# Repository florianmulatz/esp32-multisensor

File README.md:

Project archived because there is already a active GitHub project on this topic which is promising.

[GiThub Project of AIOsense](https://github.com/Schluggi/AIOsense/tree/v2.0)

Cheers

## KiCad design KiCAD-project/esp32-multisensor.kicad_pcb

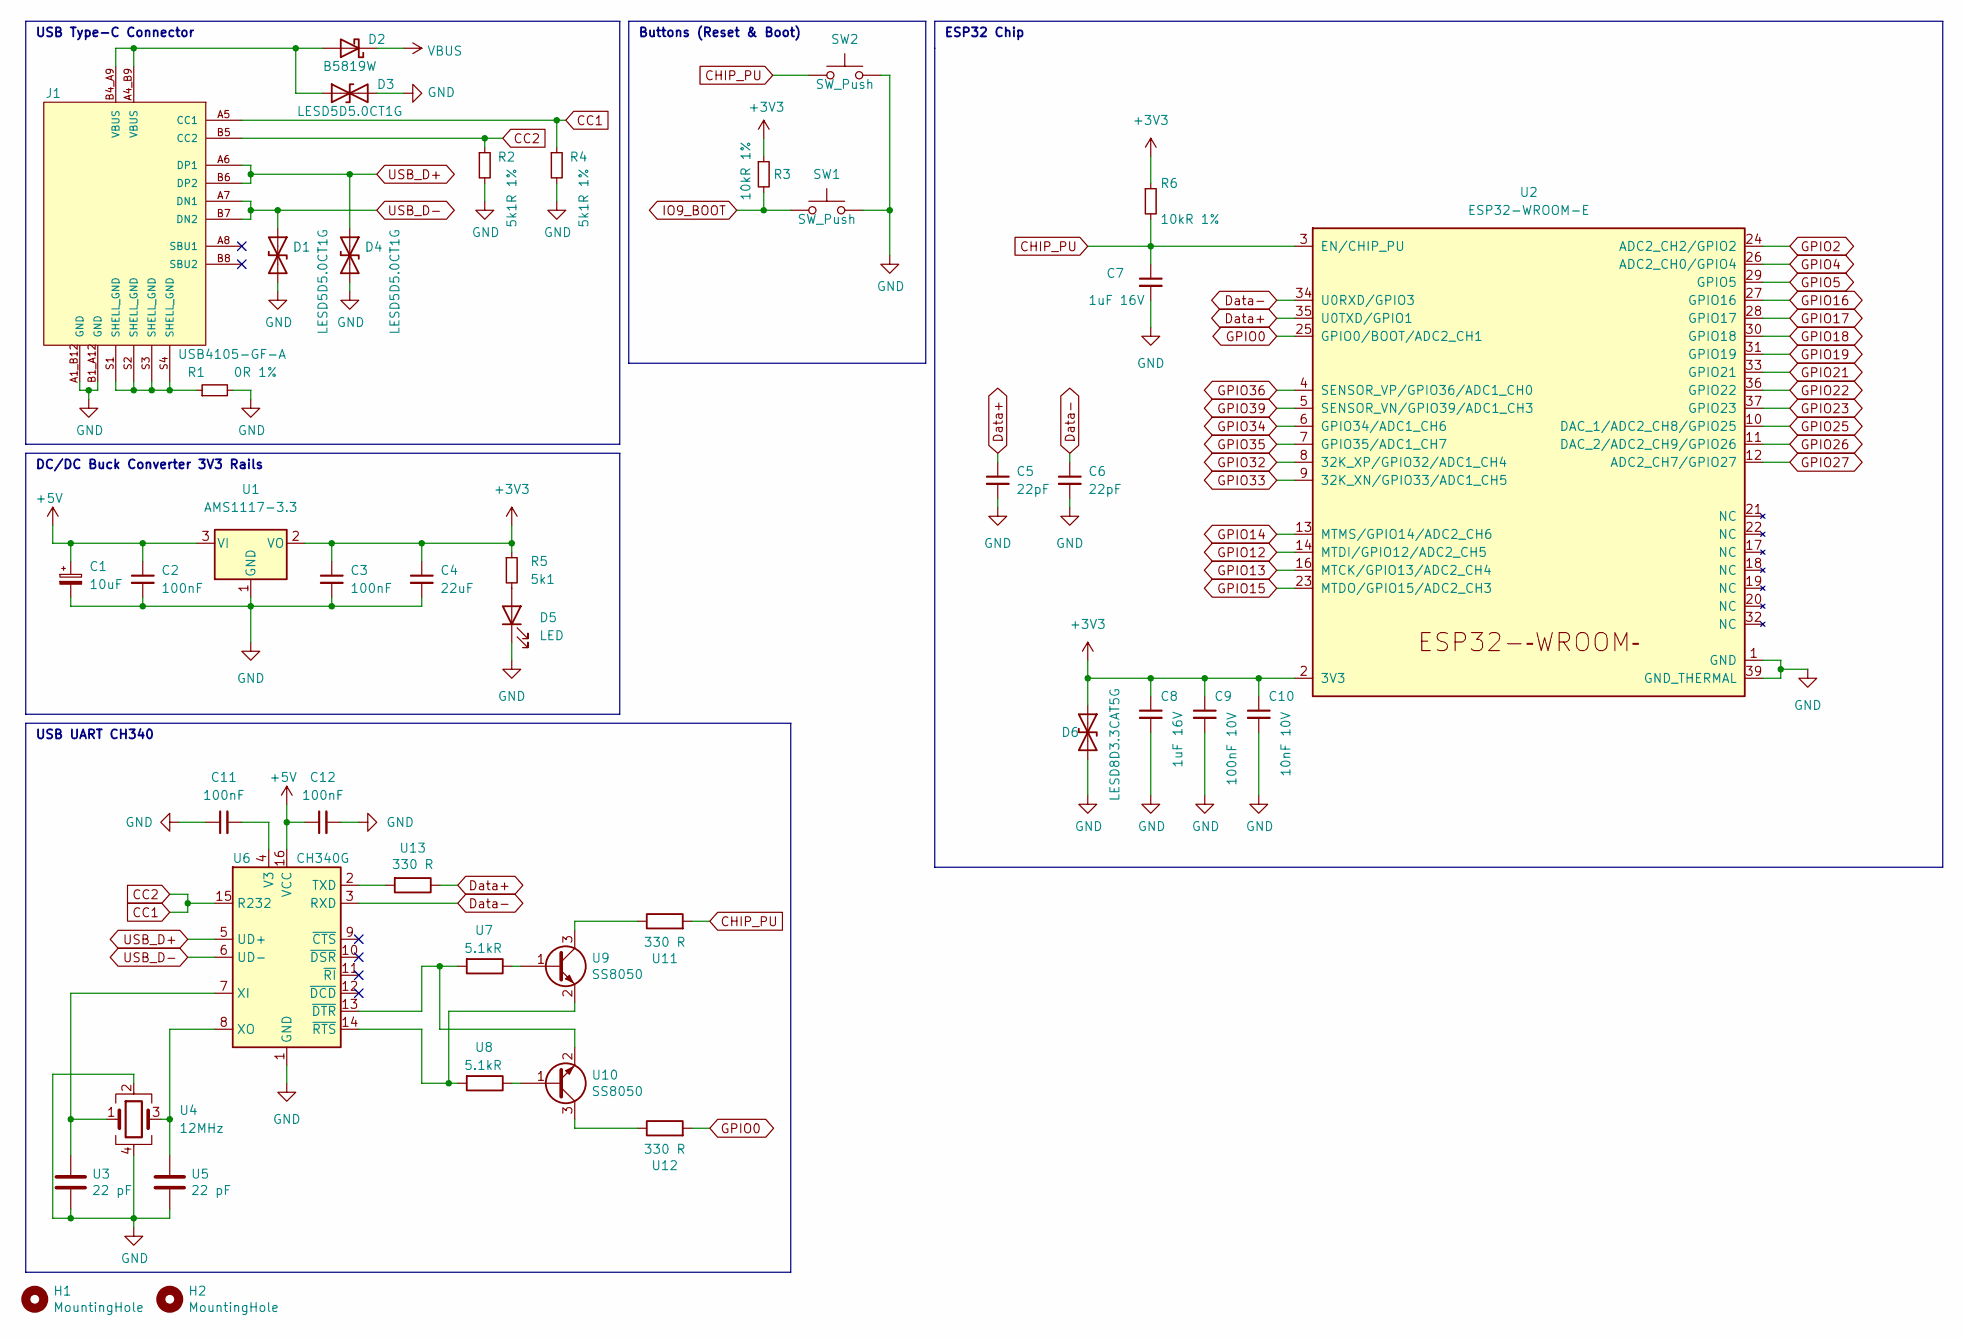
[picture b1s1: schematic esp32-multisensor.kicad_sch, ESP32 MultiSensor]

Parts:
C1: 10uF; CP_Radial_Tantal_D4.5mm_P2.50mm
C2, C3, C11, C12: 100nF; CP_Radial_D5.0mm_P2.50mm
C4: 22uF; CP_Radial_D5.0mm_P2.50mm
C5, C6: 22pF; CP_Radial_D5.0mm_P2.50mm
C7, C8: 1uF 16V; CP_Radial_D5.0mm_P2.50mm
C9: 100nF 10V; CP_Radial_D5.0mm_P2.50mm
C10: 10nF 10V; CP_Radial_D5.0mm_P2.50mm
D1, D4: LESD5D5.0CT1G; D_SOD-123; LCSC C2960981
D2: B5819W; D_A-405_P10.16mm_Horizontal; LCSC 1861420
D3: LESD5D5.0CT1G; D_SOD-923; FARNELL 3287352RL
D5: LED; LED_0805_2012Metric_Pad1.15x1.40mm_HandSolder
D6: LESD8D3.3CAT5G; SOD-882; LCSC C172409
H1, H2: MountingHole; ToolingHole_JLCSMT
J1: USB4105-GF-A; GCT_USB4105-GF-A; FARNELL 3588199
R1: 0R 1%; R_Axial_DIN0207_L6.3mm_D2.5mm_P10.16mm_Horizontal; FARNELL 2329957
R2, R4: 5k1R 1%; R_Axial_DIN0207_L6.3mm_D2.5mm_P10.16mm_Horizontal; FARNELL 2329957
R3, R6: 10kR 1%; R_Axial_DIN0207_L6.3mm_D2.5mm_P10.16mm_Horizontal; FARNELL 2329855
R5: 5k1; R_Axial_DIN0207_L6.3mm_D2.5mm_P10.16mm_Horizontal
SW1, SW2: SW_Push; SW_147873-2; LCSC C116501
U1: AMS1117-3.3; SOT-223-3_TabPin2
U2: ESP32-WROOM-E; ESP32-WROOM-32E
U3, U5: 22 pF; C_0402_1005Metric; LCSC C1555
U4: 12MHz; Crystal_SMD_3225-4Pin_3.2x2.5mm; LCSC C9002
U6: CH340G; SOIC-16_3.9x9.9mm_P1.27mm; LCSC C14267
U7, U8: 5.1kR; R_0402_1005Metric; LCSC C25905
U9, U10: SS8050; SOT-23; LCSC C2150
U11, U12, U13: 330 R; R_0402_1005Metric; LCSC C25104

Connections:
+3V3: C3.1, C4.1, C8.1, C9.1, C10.1, D6.1 (A1), R3.1, R5.1, R6.1, U1.2 (VO), U2.2 (3V3)
+5V: C1.1, C2.1, C12.1, U1.3 (VI), U6.16 (VCC)
CC1: J1.A5 (CC1), J1.B5 (CC2), R2.1, R4.1, U6.15 (R232)
CHIP_PU: C7.1, R6.2, SW2.1, U2.3 (EN/CHIP_PU), U11.2
Data+: C5.1, U2.35 (U0TXD/GPIO1), U13.1
Data-: C6.1, U2.34 (U0RXD/GPIO3), U6.3 (RXD)
GND: C1.2, C2.2, C3.2, C4.2, C5.2, C6.2, C7.2, C8.2, C9.2, C10.2, C11.1, C12.2, D1.2 (A2), D3.2 (A2), D4.2 (A2), D5.1 (K), D6.2 (A2), J1.A1_B12 (GND), J1.B1_A12 (GND), R1.2, R2.2, R4.2, SW1.2, SW2.2, U1.1 (GND), U2.1 (GND), U2.15 (GND), U2.38 (GND), U2.39 (GND_THERMAL), U3.2, U4.2, U4.4, U5.2, U6.1 (GND)
GPIO0: U2.25 (GPIO0/BOOT/ADC2_CH1), U12.2
GPIO2: U2.24 (ADC2_CH2/GPIO2)
GPIO4: U2.26 (ADC2_CH0/GPIO4)
GPIO5: U2.29 (GPIO5)
GPIO12: U2.14 (MTDI/GPIO12/ADC2_CH5)
GPIO13: U2.16 (MTCK/GPIO13/ADC2_CH4)
GPIO14: U2.13 (MTMS/GPIO14/ADC2_CH6)
GPIO15: U2.23 (MTDO/GPIO15/ADC2_CH3)
GPIO16: U2.27 (GPIO16)
GPIO17: U2.28 (GPIO17)
GPIO18: U2.30 (GPIO18)
GPIO19: U2.31 (GPIO19)
GPIO21: U2.33 (GPIO21)
GPIO22: U2.36 (GPIO22)
GPIO23: U2.37 (GPIO23)
GPIO25: U2.10 (DAC_1/ADC2_CH8/GPIO25)
GPIO26: U2.11 (DAC_2/ADC2_CH9/GPIO26)
GPIO27: U2.12 (ADC2_CH7/GPIO27)
GPIO32: U2.8 (32K_XP/GPIO32/ADC1_CH4)
GPIO33: U2.9 (32K_XN/GPIO33/ADC1_CH5)
GPIO34: U2.6 (GPIO34/ADC1_CH6)
GPIO35: U2.7 (GPIO35/ADC1_CH7)
GPIO36: U2.4 (SENSOR_VP/GPIO36/ADC1_CH0)
GPIO39: U2.5 (SENSOR_VN/GPIO39/ADC1_CH3)
IO9_BOOT: R3.2, SW1.1
unnamed: C11.2, U6.4 (V3)
unnamed: D2.2 (A), D3.1 (A1), J1.A4_B9 (VBUS), J1.B4_A9 (VBUS)
unnamed: D5.2 (A), R5.2
unnamed: J1.S1 (SHELL_GND), J1.S2 (SHELL_GND), J1.S3 (SHELL_GND), J1.S4 (SHELL_GND), R1.1
unnamed: U3.1, U4.1, U6.7 (XI)
unnamed: U4.3, U5.1, U6.8 (XO)
unnamed: U6.14 (~RTS), U8.2, U9.2 (E)
unnamed: U7.1, U9.1 (B)
unnamed: U8.1, U10.1 (B)
unnamed: U6.13 (~DTR), U7.2, U10.2 (E)
unnamed: U10.3 (C), U12.1
unnamed: U9.3 (C), U11.1
unnamed: U6.2 (TXD), U13.2
USB_D+: D4.1 (A1), J1.A6 (DP1), J1.B6 (DP2), U6.5 (UD+)
USB_D-: D1.1 (A1), J1.A7 (DN1), J1.B7 (DN2), U6.6 (UD-)
VBUS: D2.1 (K)

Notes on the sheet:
ESP32 Chip
DC/DC Buck Converter 3V3 Rails
Buttons (Reset & Boot)
USB UART CH340
USB Type-C Connector

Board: 2 copper layers, 39 parts (0 on the bottom side), 24 nets, no tracks yet.

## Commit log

2023-01-15 add .gitignore
2023-01-15 add kicad-project
2023-01-15 update folder-structure
2023-01-15 add project-specific kicad-libraries
2023-01-15 adding kicad-libraries to KiCAD project
2023-01-15 schematics added
2023-01-17 schematic created + base pcb
2023-01-19 Update READM
